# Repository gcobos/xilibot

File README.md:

# XiliBot

A self-balancing robot with a LCD screen to show faces, and a color sensor at its bottom.

In the hardware side, this repository contains the FreeCAD model, STL pieces to print, and PCB circuit desing in KiCAD.

In the software area, it includes the robot source code, which is a modified version of the [B-Robot EVO2](https://github.com/jjrobots/B-ROBOT_EVO2),
a remote controller made in Unity3D that uses [UnityOSC](https://thomasfredericks.github.io/UnityOSC) library to send commands to the robot,
and a [Web controller](web/index.html) that uses [Blockly](https://developers.google.com/blockly/) to control the robot using visual programming.
Blockly requires to start [python/webserver.py](python/server/webserver.py) to be able to send UDP packages to the robot.

This robot uses a Wemos D1 mini as the "brains", and it is configured to create its own access point, so that the controller connects to the robot's wifi.

## Xilibot standing

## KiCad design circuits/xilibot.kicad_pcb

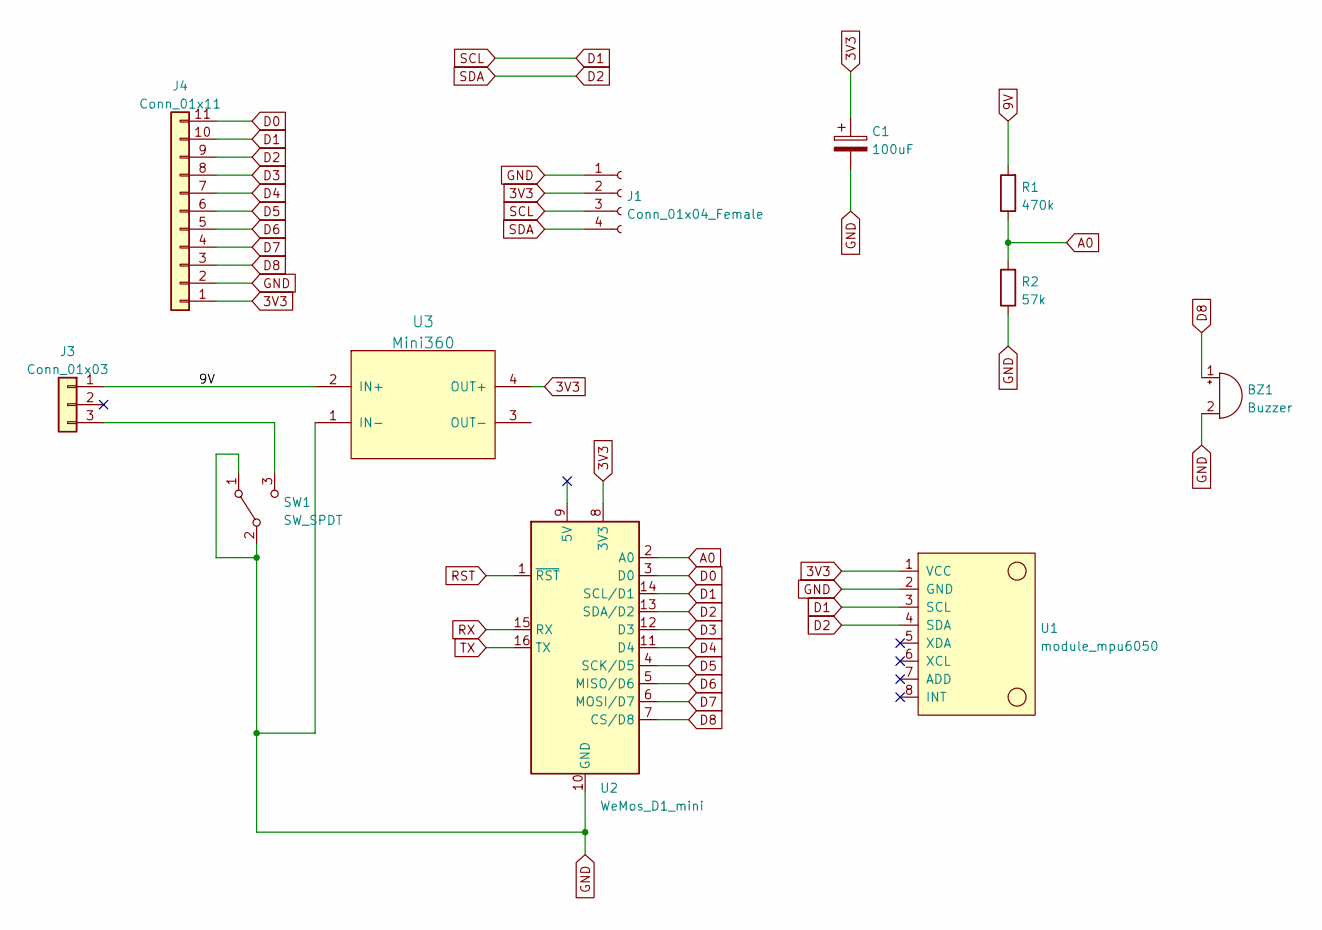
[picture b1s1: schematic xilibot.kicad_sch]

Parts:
BZ1: Buzzer; Buzzer_12x9.5RM7.6
C1: 100uF; C_Radial_D6.3mm_H5.0mm_P2.50mm
J1: Conn_01x04_Female; PinHeader_1x04_P2.54mm_Horizontal
J3: Conn_01x03; PinSocket_1x03_P2.54mm_Vertical
J4: Conn_01x11; PinSocket_1x11_P2.54mm_Vertical
R1: 470k; R_Axial_DIN0204_L3.6mm_D1.6mm_P2.54mm_Vertical
R2: 57k; R_Axial_DIN0204_L3.6mm_D1.6mm_P2.54mm_Vertical
SW1: SW_SPDT; SW_CuK_JS202011CQN_DPDT_Straight
U1: module_mpu6050
U2: WeMos_D1_mini; WEMOS_D1_mini_light
U3: Mini360; Mini360_step-down

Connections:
3V3: C1.1, J1.2, J4.1, U1.1 (VCC), U2.8 (3V3), U3.4 (OUT+)
9V: J3.1, R1.2, U3.2 (IN+)
A0: R1.1, R2.2, U2.2 (A0)
D0: J4.11, U2.3 (D0)
D1: J1.3, J4.10, U1.3 (SCL), U2.14 (SCL/D1)
D2: J1.4, J4.9, U1.4 (SDA), U2.13 (SDA/D2)
D3: J4.8, U2.12 (D3)
D4: J4.7, U2.11 (D4)
D5: J4.6, U2.4 (SCK/D5)
D6: J4.5, U2.5 (MISO/D6)
D7: J4.4, U2.6 (MOSI/D7)
D8: BZ1.1 (-), J4.3, U2.7 (CS/D8)
GND: BZ1.2 (+), C1.2, J1.1, J4.2, R2.1, SW1.1 (A), SW1.2 (B), U1.2 (GND), U2.10 (GND), U3.1 (IN-)
unnamed: J3.3, SW1.3 (C)
RST: U2.1 (~RST)
RX: U2.15 (RX)
TX: U2.16 (TX)

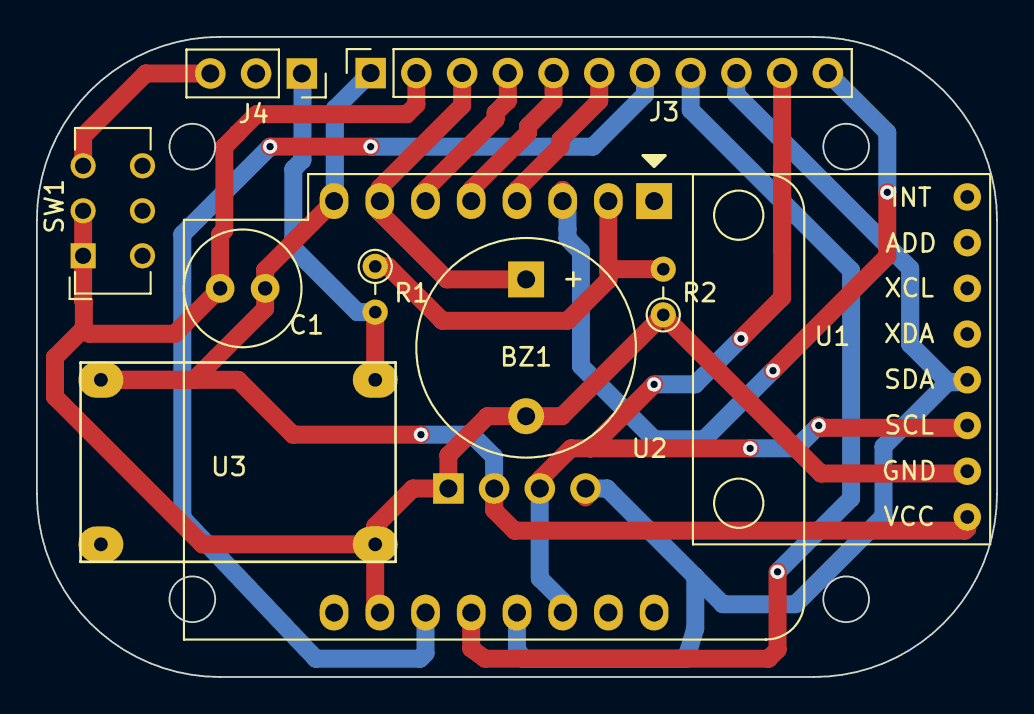
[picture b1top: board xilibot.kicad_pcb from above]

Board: 2 copper layers, 53.3 x 35.6 mm, 11 parts (1 on the bottom side), 14 nets.

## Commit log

2023-09-14 Add missing face picture
2023-09-14 First one working
2023-09-15 Color detection working, but interrupts make noise on the MPU
2023-09-20 Fixes and python classes / examples
2023-09-20 Fixes direction of throttle and target steps
2023-09-21 Set correct path for thml page + Update TODO's
2023-09-21 Include working credentials for own robot's network
2023-09-28 Prepare blockly translations and set new faces
2023-09-28 Set credentials for the robot's AP
2023-10-15 Add CAD and circuits
2023-10-27 Add README
2023-10-27 README fixes
2023-10-27 Add Unity remote controller
